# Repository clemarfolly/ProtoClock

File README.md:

# ProtoClock

Relógio digital com alarme para **PIC16F84**, construído com componentes simples e disponíveis.

## Funcionalidades

- Relógio com 4 displays de 7 segmentos (HH:MM)
- Ponto decimal piscando (1Hz)
- Alarme configurável (hora e minuto)
- Brilho dos displays controlado por PWM
- Calibração fina do timer via osciloscópio

## Hardware

### Componentes

| Componente | Descrição | Quantidade |
|------------|-----------|------------|
| PIC16F84 | Microcontrolador | 1 |
| 4017 | Decodificador decimal | 1 |
| 74HC08 | Quad AND gate | 1 |
| BC558 | Transistor PNP | 1 |
| LTS-6960HR | Display 7 segmentos | 4 |
| BZ1 | Buzzer | 1 |
| Y1 | Cristal 4MHz | 1 |
| R1-R3 | 10kΩ (pull-up botões) | 3 |
| R4 | 1kΩ (base transistor) | 1 |
| R5-R12 | 220Ω (segmentos) | 8 |
| C1-C2 | 22pF (cristal) | 2 |
| C3-C4 | 100nF (desacoplamento) | 2 |
| C5 | 10µF (alimentação) | 1 |
| D1-D2 | LED (ponto decimal) | 2 |
| D3 | 1N4007 (proteção buzzer) | 1 |

### Pinagem

```
PIC16F84
┌────────────────────┐
│ 1 RA2   SPK/MIN   │ ← Speaker + Botão MIN (compartilhado)
│ 2 RA3   PONTO/ALR  │ ← LED Ponto + Botão ALARME (compartilhado)
│ 3 RA4   HORA       │ ← Botão HORA
│ 4 MCLR  RESET      │ ← Reset (10k pull-up)
│ 5 VSS   GND        │
│ 6 RB0              │ → Segmento a
│ 7 RB1              │ → Segmento b
│ 8 RB2              │ → Segmento c
│ 9 RB3              │ → PWM Brilho (74HC08)
│ 10 RB4             │ → Segmento d
│ 11 RB5             │ → Segmento e
│ 12 RB6             │ → Segmento f
│ 13 RB7             │ → Segmento g
│ 14 VDD   +5V       │
│ 15 OSC2            │ ← Cristal 4MHz
│ 16 OSC1            │ ← Cristal 4MHz
│ 17 RA0             │ → 4017 CLK
│ 18 RA1             │ → 4017 RESET
└────────────────────┘
```

### Esquemático

O esquemático completo está em [`ProtoClock.pdf`](ProtoClock.pdf).

## Firmware

### Arquivos

| Arquivo | Descrição |
|---------|-----------|
| `ProtoClock84_Otimizado.c` | Código fonte principal (PIC16F84) |
| `ProtoClock.c` | Código original (PIC16F628A, referência) |
| `c84_Otimizado.bat` | Script de compilação |
| `analise_memoria.py` | Análise de uso de memória |

### Estrutura do Código

```
├── Macros e Defines
│   ├── BIT_SET/CLEAR/FLIP/CHECK — manipulação de bits
│   ├── RESET_4017/CLOCK_4017 — controle do decodificador
│   └── SPK_* — configuração do speaker
│
├── Variáveis Globais
│   ├── Relógio: segundo, minuto, hora
│   ├── Alarme: alarme_minuto, alarme_hora, toca_alarme
│   └── Botões: pushFlag[], pushState[]
│
├── ISR (Interrupção)
│   └── Timer0 ~1ms: contagem de tempo, PWM, speaker
│
├── task1() — 61ms
│   ├── Contagem de tempo (segundo/minuto/hora)
│   ├── Leitura de botões com debounce
│   └── Desligamento do alarme
│
├── task2() — 5ms
│   └── Multiplexação dos displays (4017)
│
├── task3() — 201ms
│   └── Ações dos botões (ajuste tempo/alarme)
│
└── main()
    ├── Inicialização
    ├── Loop principal
    └── Lógica do alarme
```

### Compilação

**Requisitos:**
- [SDCC 4.3.0](http://sdcc.sourceforge.net/) (compilador C para PIC)
- [gputils](http://gputils.sourceforge.net/) (montador e linker)

**Passos:**

```bash
# Compilar (Windows)
c84_Otimizado.bat

# Ou manualmente:
sdcc -S --use-non-free -mpic14 -p16f84 ProtoClock84_Otimizado.c
gpasm -I C:\Programas\gputils\header -o ProtoClock84_Otimizado.o -c ProtoClock84_Otimizado.asm
gplink -O 2 -f 0x00 -r -m -s C:\Programas\gputils\lkr\16f84_g.lkr -o ProtoClock84_Otimizado.hex ProtoClock84_Otimizado.o C:\Programas\SDCC\lib\pic14\libsdcc.lib C:\Programas\SDCC\non-free\lib\pic14\pic16f84.lib
```

**Análise de memória:**

```bash
python analise_memoria.py ProtoClock84_Otimizado.map
```

Saída:
```
--- Program Memory ---
  Codigo real:      930 words  (90.8% da ROM)
  Espaco livre:      94 words  (9.2%)

--- Data Memory ---
  RAM utilizada:   57 bytes / 68 bytes
```

### Calibração do Timer

O cristal de 4MHz não é preciso. O Timer0 precisa de calibração fina:

1. Defina `#define CALIBRACAO 1` no código
2. Compile e grave no PIC
3. Meça a frequência no pino RA3 com osciloscópio
4. Ajuste o valor de `cal` em `main()` até obter ~500Hz (2ms período)
5. Remova `#define CALIBRACAO 1`
6. Recompile

Valor padrão: `cal = 10` (ajustado para ~501Hz)

## Botões

| Botão | Pino | Função |
|-------|------|--------|
| HORA | RA4 | Ajustar hora / Desligar alarme |
| MIN | RA2 | Ajustar minuto / Desligar alarme* |
| ALARME | RA3 | Segurar para ver/ajustar alarme |

### Operação

**Ver horário:** Exibição padrão nos displays.

**Ajustar relógio:**
- Toque rápido em HORA ou MIN = incrementa 1
- Segurar HORA ou MIN = incremento rápido

**Configurar alarme:**
1. Segurar botão ALARME
2. Enquanto segura, tocar HORA ou MIN para ajustar
3. Displays mostram o horário do alarme
4. Soltar ALARME volta ao horário

**Alarme desabilitado:** Hora = 0 e Minuto = 0

**Desligar alarme:** Pressionar HORA ou ALARME enquanto toca.

> \* **Nota:** O botão MIN compartilha pino RA2 com o speaker. Enquanto o alarme toca, o MIN não funciona. Apenas HORA e ALARME podem desligar.

## Limitações de Hardware

### Pinos Compartilhados

| Pino | Funções | Conflito |
|------|---------|----------|
| RA2 | Speaker + Botão MIN | Botão MIN inoperante durante alarme |
| RA3 | LED Ponto + Botão ALARME | LED desligado durante leitura do botão |

### Soluções implementadas

- **RA2:** Botão MIN é ignorado enquanto `toca_alarme > 0`
- **RA3:** Pin é alternado entre saída (LED) e entrada (botão) ciclicamente a cada ~61ms

### Recomendações para versão futura

- Usar pinos dedicados para speaker e botões
- Adicionar capacitor 100nF entre MCLR e GND para reset mais confiável
- Considerar PIC16F628A (mais pinos, BOR interno)

## Memória

| Recurso | Total | Utilizado | Livre |
|---------|-------|-----------|-------|
| ROM (programa) | 1024 words | 930 words | 94 words |
| RAM (dados) | 68 bytes | 57 bytes | 11 bytes |

### Distribuição da ROM

| Seção | Tamanho | Descrição |
|-------|---------|-----------|
| task1 | 286w | Leitura de botões + relógio |
| task3 | 164w | Ações dos botões |
| main | 145w | Loop principal + alarme |
| ISR | 129w | Interrupção (Timer0) |
| task2 | 124w | Multiplexação display |
| .code | 19w | Biblioteca _gptrget1 |
| obterNumeroDisplay | 18w | Conversão display |
| obterDecimal | 15w | Extração dezena |
| obterUnidade | 13w | Extração unidade |
| numero[10] | 10w | Tabela de segmentos |
| botaoIO[3] | 3w | Mapeamento botões |

## Esquemático

O esquemático completo está disponível em [`ProtoClock.pdf`](ProtoClock.pdf).

Feito com KiCad E.D.A. 9.0.7.

## Licença

Este é um projeto pessoal. Use como quiser.

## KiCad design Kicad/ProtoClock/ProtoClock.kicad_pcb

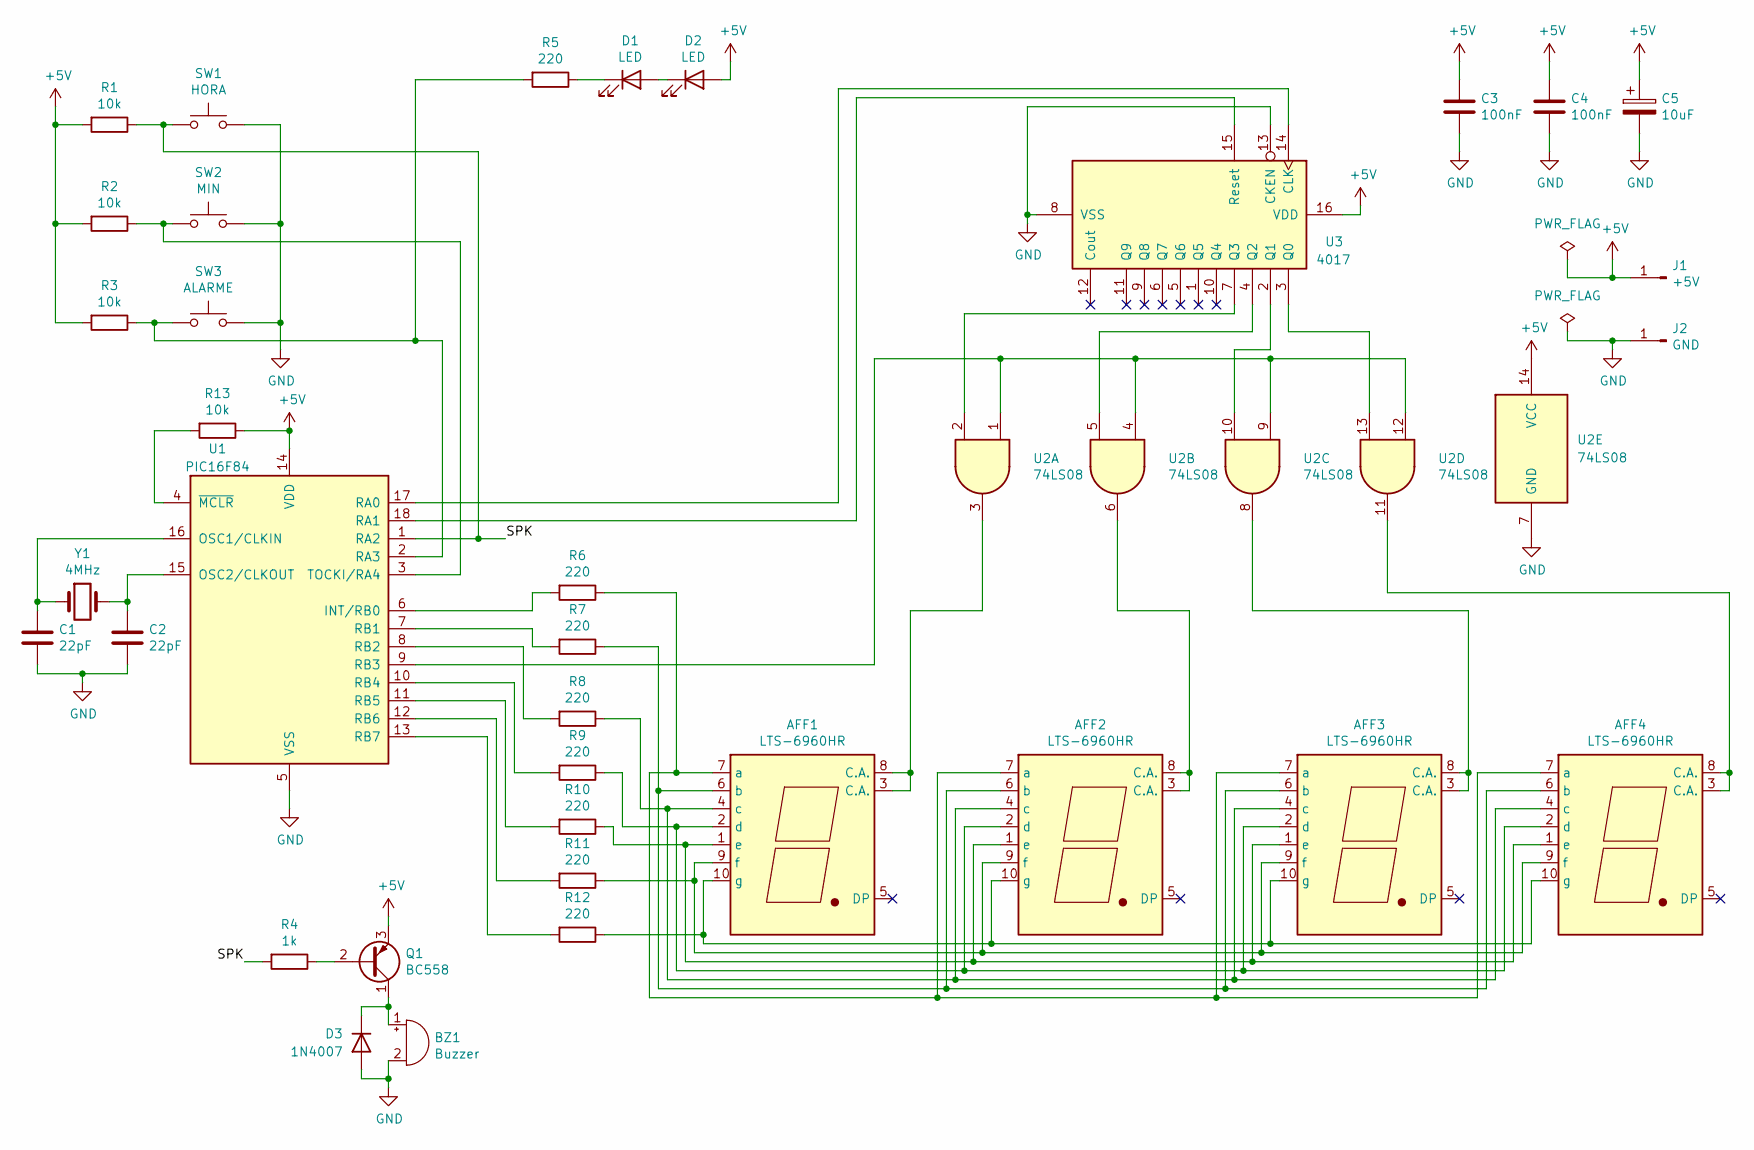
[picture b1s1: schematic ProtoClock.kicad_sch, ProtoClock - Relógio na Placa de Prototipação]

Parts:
AFF1, AFF2, AFF3, AFF4: LTS-6960HR; 7SegmentLED_LTS6760_LTS6780
BZ1: Buzzer; Buzzer_12x9.5RM7.6
C1, C2: 22pF; C_Disc_D3.0mm_W1.6mm_P2.50mm
C3, C4: 100nF; C_Disc_D3.0mm_W1.6mm_P2.50mm
C5: 10uF; CP_Radial_D5.0mm_P2.50mm
D1, D2: LED; LED_D3.0mm
D3: 1N4007; D_T-1_P5.08mm_Horizontal
J1: +5V; Pin_D1.0mm_L10.0mm
J2: GND; Pin_D1.0mm_L10.0mm
Q1: BC558; TO-92_Inline_Wide
R1, R2, R3, R13: 10k; R_Axial_DIN0204_L3.6mm_D1.6mm_P5.08mm_Horizontal
R4: 1k; R_Axial_DIN0204_L3.6mm_D1.6mm_P5.08mm_Horizontal
R5, R6, R7, R8, R9, R10, R11, R12: 220; R_Axial_DIN0204_L3.6mm_D1.6mm_P5.08mm_Horizontal
SW1: HORA; SW_PUSH_6mm
SW2: MIN; SW_PUSH_6mm
SW3: ALARME; SW_PUSH_6mm
U1: PIC16F84; DIP-18_W7.62mm_Socket_LongPads
U2: 74LS08; DIP-14_W7.62mm_Socket_LongPads
U3: 4017; DIP-16_W7.62mm_Socket_LongPads
Y1: 4MHz; Resonator-2Pin_W10.0mm_H5.0mm

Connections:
+5V: C3.2, C4.1, C5.1, D2.2 (A), J1.1, Q1.3 (E), R1.2, R2.2, R3.2, R13.1, U1.14 (VDD), U2.14 (VCC), U3.16 (VDD)
/SPK: R1.1, R4.2, SW1.1, U1.1 (RA2)
GND: BZ1.2 (-), C1.2, C2.2, C3.1, C4.2, C5.2, D3.2 (A), J2.1, SW1.2, SW2.2, SW3.2, U1.5 (VSS), U2.7 (GND), U3.8 (VSS), U3.13 (CKEN)
unnamed: AFF1.3 (C.A.), AFF1.8 (C.A.), U2.3
unnamed: AFF1.7 (a), AFF2.7 (a), AFF3.7 (a), AFF4.7 (a), R6.1
unnamed: AFF1.6 (b), AFF2.6 (b), AFF3.6 (b), AFF4.6 (b), R7.1
unnamed: AFF1.4 (c), AFF2.4 (c), AFF3.4 (c), AFF4.4 (c), R8.1
unnamed: AFF1.2 (d), AFF2.2 (d), AFF3.2 (d), AFF4.2 (d), R9.1
unnamed: AFF1.1 (e), AFF2.1 (e), AFF3.1 (e), AFF4.1 (e), R10.1
unnamed: AFF1.9 (f), AFF2.9 (f), AFF3.9 (f), AFF4.9 (f), R11.1
unnamed: AFF1.10 (g), AFF2.10 (g), AFF3.10 (g), AFF4.10 (g), R12.1
unnamed: AFF2.3 (C.A.), AFF2.8 (C.A.), U2.6
unnamed: AFF3.3 (C.A.), AFF3.8 (C.A.), U2.8
unnamed: AFF4.3 (C.A.), AFF4.8 (C.A.), U2.11
unnamed: BZ1.1 (+), D3.1 (K), Q1.1 (C)
unnamed: D1.2 (A), D2.1 (K)
unnamed: D1.1 (K), R5.1
unnamed: Q1.2 (B), R4.1
unnamed: R6.2, U1.6 (INT/RB0)
unnamed: C1.1, U1.16 (OSC1/CLKIN), Y1.1
unnamed: C2.1, U1.15 (OSC2/CLKOUT), Y1.2
unnamed: U1.17 (RA0), U3.14 (CLK)
unnamed: U1.18 (RA1), U3.15 (Reset)
unnamed: R3.1, R5.2, SW3.1, U1.2 (RA3)
unnamed: R7.2, U1.7 (RB1)
unnamed: R8.2, U1.8 (RB2)
unnamed: U1.9 (RB3), U2.1, U2.4, U2.9, U2.12
unnamed: R9.2, U1.10 (RB4)
unnamed: R10.2, U1.11 (RB5)
unnamed: R11.2, U1.12 (RB6)
unnamed: R12.2, U1.13 (RB7)
unnamed: R2.1, SW2.1, U1.3 (TOCKI/RA4)
unnamed: R13.2, U1.4 (~MCLR)
unnamed: U2.13, U3.3 (Q0)
unnamed: U2.10, U3.2 (Q1)
unnamed: U2.5, U3.4 (Q2)
unnamed: U2.2, U3.7 (Q3)

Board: 2 copper layers, 36 parts (0 on the bottom side), 37 nets, no tracks yet.

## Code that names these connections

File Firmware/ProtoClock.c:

#include <pic16f628a.h>
#include <stdint.h>

static __code uint16_t __at (_CONFIG) configword1 = _CP_OFF & _WDT_OFF & _HS_OSC & _MCLRE_OFF & _LVP_OFF;

#define true 1
#define false 0
#define ligado 1
#define desligado 0

#define NoPush 1 
#define MaybePush 2
#define Pushed 3
#define MaybeNoPush 4

/* a=target variable, b=bit number to act upon 0-n */
#define BIT_SET(a,b) ((a) |= (1<<(b)))
#define BIT_CLEAR(a,b) ((a) &= ~(1<<(b)))
#define BIT_FLIP(a,b) ((a) ^= (1<<(b)))
#define BIT_CHECK(a,b) ((a) & (1<<(b)))

#define nop() __asm nop __endasm

#define RESET_4017() BIT_SET(PORTA, 1); nop(); nop(); BIT_CLEAR(PORTA, 1)
#define CLOCK_4017() BIT_SET(PORTA, 0); nop(); nop(); BIT_CLEAR(PORTA, 0)

#define PONTO RA3
#define SKP RA2
#define SPK_PIN 2
#define SPK_PORT PORTA
#define SPK_PORT_DEF TRISA

void _sdcc_gsinit_startup(void)
{
  __asm pagesel _main __endasm;
  __asm goto _main __endasm;
}

const uint8_t numero[11] = { 0b10000000,
							 0b11110001,
							 0b01000100,
							 0b01100000,
							 0b00110001,
							 0b00100010,
							 0b00000010,
							 0b11110000,
							 0b00000000,
							 0b00100000,
  							 0b11110111};

uint8_t segundo;
uint8_t minuto;
uint8_t hora;
volatile uint16_t tempo;
uint8_t display;

uint8_t alarme_minuto;
uint8_t alarme_hora;
uint8_t toca_alarme;
uint8_t alarme_desligado_manualmente;


#define TOTAL_BOTOES 3
const uint8_t botaoIO[TOTAL_BOTOES] = {2, 4, 5};
uint8_t pushFlag[TOTAL_BOTOES];
uint8_t pushState[TOTAL_BOTOES];

#define BOTAO_MINUTO	0
#define BOTAO_HORA		1
#define BOTAO_ALARME	2

#define FLAG_BOTAO_ND		0
#define FLAG_BOTAO_SOLTO	255
#define FLAG_BOTAO_SEGURO	2000 / TEMPO_TASK1_DEF 

#define BOTAO_ALARME_PRESSIONADO (pushFlag[BOTAO_ALARME] > FLAG_BOTAO_ND && pushFlag[BOTAO_ALARME] < FLAG_BOTAO_SOLTO)
#define ALARME_DESLIGADO (alarme_hora == 0 && alarme_minuto == 0)
							 
#define TEMPO_TASK1_DEF 61
#define TEMPO_TASK2_DEF 10
#define TEMPO_TASK3_DEF 201
 
volatile uint8_t tempo_task1;
volatile uint8_t tempo_task2;
volatile uint8_t tempo_task3;

void Intr(void) __interrupt 0
{
	//timer0 executando a cada 1mS
	if (T0IF)
	{
		TMR0 = 6;
		T0IF = 0;
		
		if (tempo_task1 > 0)
			tempo_task1--;

		if (tempo_task2 > 0)
			tempo_task2--;

		if (tempo_task3 > 0)
			tempo_task3--;
	
		tempo++;
		
		if (toca_alarme && PONTO)
			BIT_FLIP(SPK_PORT, SPK_PIN);
	}
}

void task1()
{
	uint8_t ps, btn_pres, pf;
	uint8_t i;
	
	if (tempo > 1000)
	{
		tempo -= 1000;
		
		segundo++;
		
		if (segundo > 59)
		{
			segundo = 0;
			minuto++;
		}
		
		if (minuto > 59)
		{
			minuto = 0;
			hora++;
		}
		
		if (hora > 23)
			hora = 0;
	}

	for (i = 0; i < TOTAL_BOTOES; i++)
	{
		ps = pushState[i];
		pf = pushFlag[i];
		btn_pres = !BIT_CHECK(PORTA, botaoIO[i]);
		switch (ps)
		{
		case NoPush: 
			if (btn_pres) 
			{
				pf = FLAG_BOTAO_ND;
				ps = MaybePush;
			}
			else 
				ps = NoPush;
			break;
		case MaybePush:
			if (btn_pres)
			{
				ps = Pushed;   
				pf = 1;
			}
			else 
				ps = NoPush;
			break;
		case Pushed:  
			if (btn_pres) 
			{
				ps = Pushed; 

				if (pf < (FLAG_BOTAO_SOLTO-1))
					pf++;
			}
			else 
				ps = MaybeNoPush;    
			break;
		case MaybeNoPush:
			if (btn_pres) 
				ps = Pushed; 
			else 
			{
				ps = NoPush;
				pf = FLAG_BOTAO_SOLTO;
			}
			break;
		}
		pushState[i] = ps;
		pushFlag[i] = pf;
	}
}

void task2()
{
	PORTB = numero[10] | (1<<3);
	CLOCK_4017();
	
	if (display == 0)
	{
		RESET_4017();
		
		if (BOTAO_ALARME_PRESSIONADO)
			PORTB = numero[alarme_minuto % 10] | (1<<3);
		else
			PORTB = numero[minuto % 10] | (1<<3);
		display++;
	}
	else if (display == 1)
	{
		if (BOTAO_ALARME_PRESSIONADO)
			PORTB = numero[alarme_minuto / 10] | (1<<3);
		else
			PORTB = numero[minuto / 10] | (1<<3);
		display++;
	}	
	else if (display == 2)
	{
		if (BOTAO_ALARME_PRESSIONADO)
			PORTB = numero[alarme_hora % 10] | (1<<3);
		else
			PORTB = numero[hora % 10] | (1<<3);
		display++;
	}
	else if (display == 3)
	{
		if (BOTAO_ALARME_PRESSIONADO)
		{
			if ((alarme_hora / 10) == 0)
				PORTB = numero[10] | (1<<3);
			else
				PORTB = numero[alarme_hora / 10] | (1<<3);
		}
		else
		{
			if ((hora / 10) == 0)
				PORTB = numero[10] | (1<<3);
			else
				PORTB = numero[hora / 10] | (1<<3);
		}
		display = 0;
	}
}

void task3()
{
	if (pushFlag[BOTAO_MINUTO] > FLAG_BOTAO_SEGURO)
	{
		if (pushFlag[BOTAO_MINUTO] == FLAG_BOTAO_SOLTO)
			pushFlag[BOTAO_MINUTO] = FLAG_BOTAO_ND;
		
		if (toca_alarme)
		{
			toca_alarme = 0;
			alarme_desligado_manualmente = 1;
		}
		else
		{
			if (BOTAO_ALARME_PRESSIONADO)
			{
				alarme_minuto++;		
				
				if (alarme_minuto > 59)
					alarme_minuto = 0;
			}
			else 
			{
				segundo = 0;
				minuto++;		
				
				if (minuto > 59)
					minuto = 0;
			}
		}
		
	}
	else if (pushFlag[BOTAO_HORA] > FLAG_BOTAO_SEGURO)
	{
		if (pushFlag[BOTAO_HORA] == FLAG_BOTAO_SOLTO)
			pushFlag[BOTAO_HORA] = FLAG_BOTAO_ND;

		if (toca_alarme)
		{
			toca_alarme = 0;		
			alarme_desligado_manualmente = 1;
		}
		else
		{
			if (BOTAO_ALARME_PRESSIONADO)
			{
				alarme_hora++;		
				
				if (alarme_hora > 23)
					alarme_hora = 0;
			}
			else
			{
				hora++;		
				
				if (hora > 23)
					hora = 0;
			}
		}

	}
}

void main()
{
	uint8_t i;
	
	TRISB = 0;
	TRISA = 0b00110100;

	PORTB = 0;
	PORTA = 0;
  
	//timer0 configurado 1ms
	OPTION_REG &= 0xC0 | 0x01;
	TMR0 = 6;
	T0IE = 1;
	GIE = 1;

	RB3 = 1;
  
	tempo_task1 = TEMPO_TASK1_DEF;
	tempo_task2 = TEMPO_TASK2_DEF;
	tempo_task3 = TEMPO_TASK3_DEF;

	display = 0;

	for (i = 0; i < TOTAL_BOTOES; i++)
	{
		pushFlag[i] = FLAG_BOTAO_ND;
		pushState[i] = NoPush;
	}
	
  for (;;) 
  {
    if (tempo_task1 == 0)
	{
		tempo_task1 = TEMPO_TASK1_DEF;
		task1();
	}
	
	if (tempo_task2 == 0)
	{
		tempo_task2 = TEMPO_TASK2_DEF;
		task2();
	}

	if (tempo_task3 == 0)
	{
		tempo_task3 = TEMPO_TASK3_DEF;
		task3();
	}
	
	if (!ALARME_DESLIGADO && !alarme_desligado_manualmente && (hora == alarme_hora) && (minuto == alarme_minuto))
	{
		BIT_CLEAR(SPK_PORT_DEF, SPK_PIN);
		toca_alarme = 1;
	}
	else
	{
		BIT_SET(SPK_PORT_DEF, SPK_PIN);
		toca_alarme = 0;
	}
	
	if (alarme_desligado_manualmente && (minuto > alarme_minuto || (minuto == 0 && alarme_minuto == 59)))
		alarme_desligado_manualmente = 0;
	
	PONTO = (tempo < 500) ? 0 : 1;
	
	
  }
}
